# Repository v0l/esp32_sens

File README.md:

# esp32_sens
ESP32 sensor breakout board (I2C)

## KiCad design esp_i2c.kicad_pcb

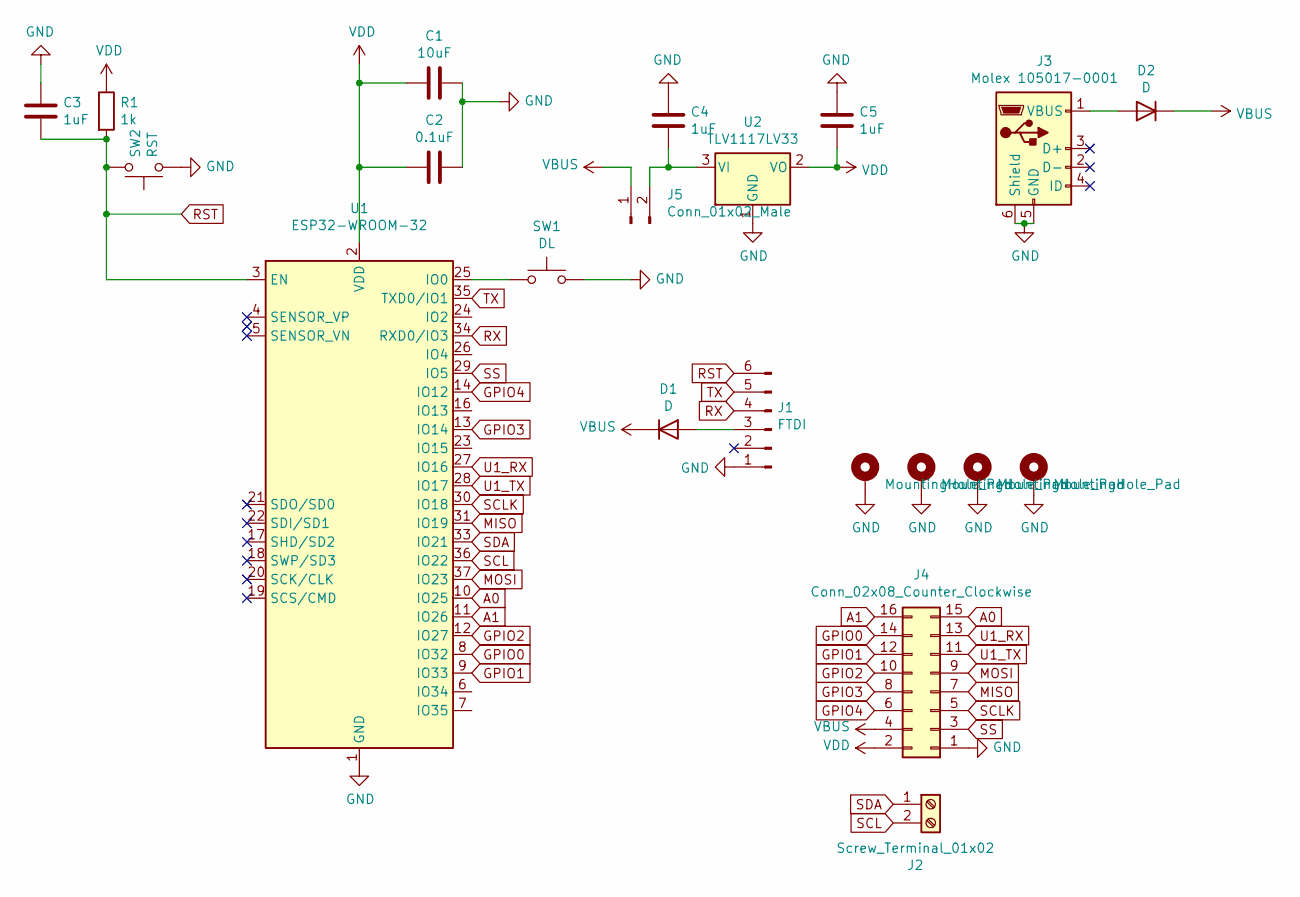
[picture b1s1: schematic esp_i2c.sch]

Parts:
C1: 10uF; C_0805_2012Metric_Pad1.18x1.45mm_HandSolder
C2: 0.1uF; C_0805_2012Metric_Pad1.18x1.45mm_HandSolder
C3, C4, C5: 1uF; C_0805_2012Metric_Pad1.18x1.45mm_HandSolder
D1, D2: D; D_SOD-323
H1, H2, H3, H4: MountingHole_Pad; MountingHole_3.2mm_M3_ISO7380_Pad
J1: FTDI; PinHeader_1x06_P2.54mm_Vertical
J2: Screw_Terminal_01x02; TerminalBlock_Phoenix_PT-1,5-2-5.0-H_1x02_P5.00mm_Horizontal
J3: Molex 105017-0001; USB_Micro-B_Molex-105017-0001
J4: Conn_02x08_Counter_Clockwise; PinHeader_2x08_P2.54mm_Vertical
J5: Conn_01x02_Male; PinHeader_1x02_P2.54mm_Vertical
R1: 1k; R_0805_2012Metric_Pad1.20x1.40mm_HandSolder
SW1: DL; SW_PUSH_6mm_H5mm
SW2: RST; SW_PUSH_6mm_H5mm
U1: ESP32-WROOM-32
U2: TLV1117LV33; SOT-223

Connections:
A0: J4.15, U1.10 (IO25)
A1: J4.16, U1.11 (IO26)
GND: C1.2, C2.2, C3.1, C4.1, C5.1, H1.1, H2.1, H3.1, H4.1, J1.1, J3.5 (GND), J3.6 (Shield), J4.1, SW1.2, SW2.1, U1.1 (GND), U1.15 (GND), U1.38 (GND), U1.39 (GND), U2.1 (GND)
GPIO0: J4.14, U1.8 (IO32)
GPIO1: J4.12, U1.9 (IO33)
GPIO2: J4.10, U1.12 (IO27)
GPIO3: J4.8, U1.13 (IO14)
GPIO4: J4.6, U1.14 (IO12)
MISO: J4.7, U1.31 (IO19)
MOSI: J4.9, U1.37 (IO23)
unnamed: C4.2, J5.2, U2.3 (VI)
unnamed: D1.2 (A), J1.3
unnamed: D2.2 (A), J3.1 (VBUS)
unnamed: SW1.1, U1.25 (IO0)
RST: C3.2, J1.6, R1.2, SW2.2, U1.3 (EN)
RX: J1.4, U1.34 (RXD0/IO3)
SCL: J2.2, U1.36 (IO22)
SCLK: J4.5, U1.30 (IO18)
SDA: J2.1, U1.33 (IO21)
SS: J4.3, U1.29 (IO5)
TX: J1.5, U1.35 (TXD0/IO1)
U1_RX: J4.13, U1.27 (IO16)
U1_TX: J4.11, U1.28 (IO17)
VBUS: D1.1 (K), D2.1 (K), J4.4, J5.1
VDD: C1.1, C2.1, C5.2, J4.2, R1.1, U1.2 (VDD), U2.2 (VO), U2.4

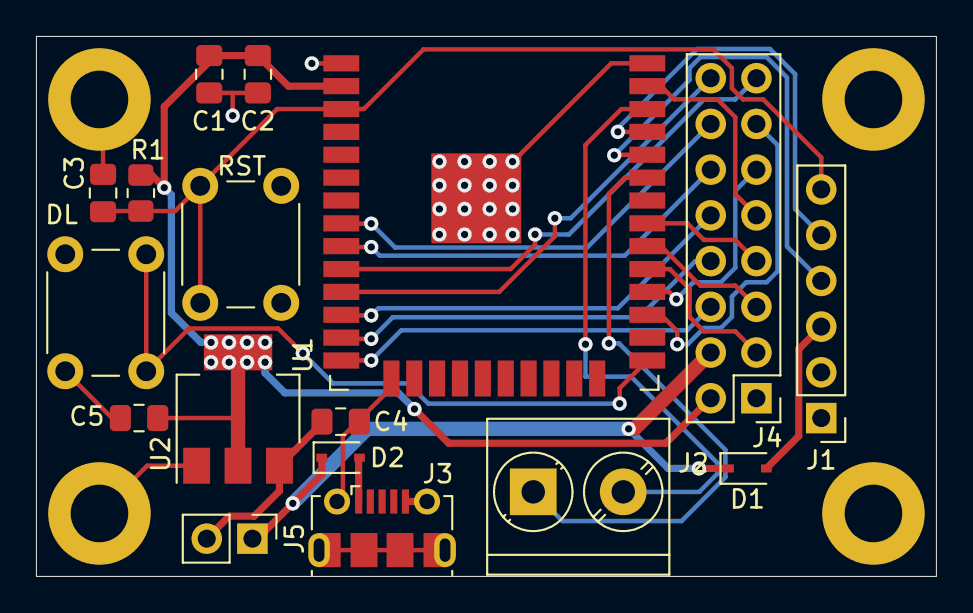
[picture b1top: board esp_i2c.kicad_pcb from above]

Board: 2 copper layers, 50.0 x 30.0 mm, 21 parts (0 on the bottom side), 25 nets.

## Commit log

2021-03-15 Init esp32_sens
2021-03-24 v0.2
